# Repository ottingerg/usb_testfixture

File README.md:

# USB-C HighSpeed Test Fixture

This is a simple test fixture for testing Highspeed (USB 2.0) on USB-C Connectors

## How To Build

This board is intended to be manufactured on 2 Layers with 0.8 mm prepreg.

First prototypes are made with OSHPARK "2oz-0.8mm" process

Needed Parts:

1 pcs. Wuerth Elektronik 632712000011 (USB-C Connector)
2 pcs. Rosenberger 32K243-40ML5 (SMA Connector)

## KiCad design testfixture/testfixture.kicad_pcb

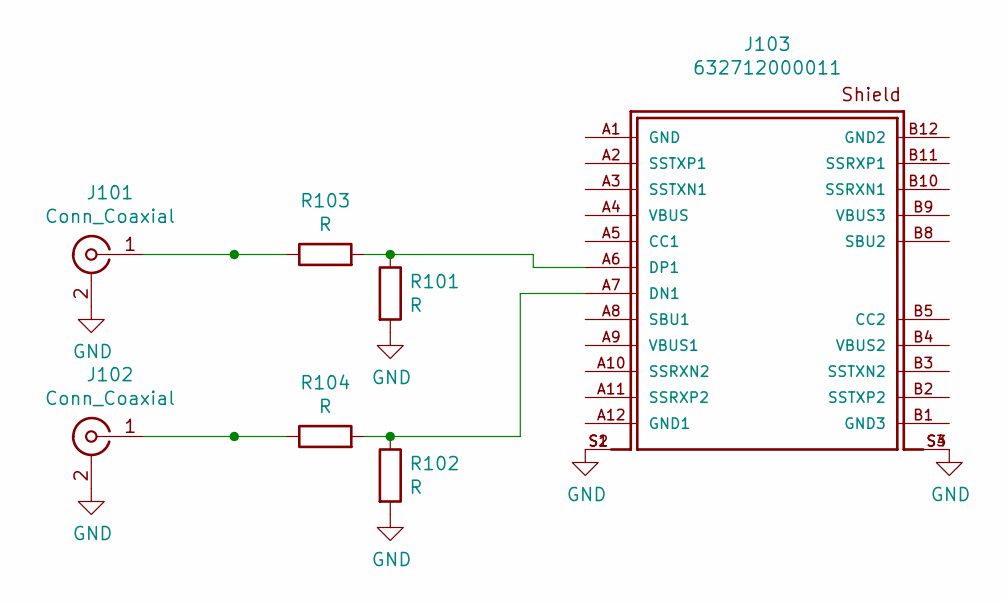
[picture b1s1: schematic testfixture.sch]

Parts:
J101, J102: Conn_Coaxial; 32K243-40ML5
J103: 632712000011; PART-NUMBER 632712000011
R101, R102, R103, R104: R; R_0402_1005Metric

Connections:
GND: J101.2 (Ext), J102.2 (Ext), J103.S1, J103.S2, J103.S3, J103.S4, R101.2, R102.2
unnamed: J101.1 (In), R103.1
unnamed: J102.1 (In), R104.1
unnamed: J103.A6 (DP1), R101.1, R103.2
unnamed: J103.A7 (DN1), R102.1, R104.2

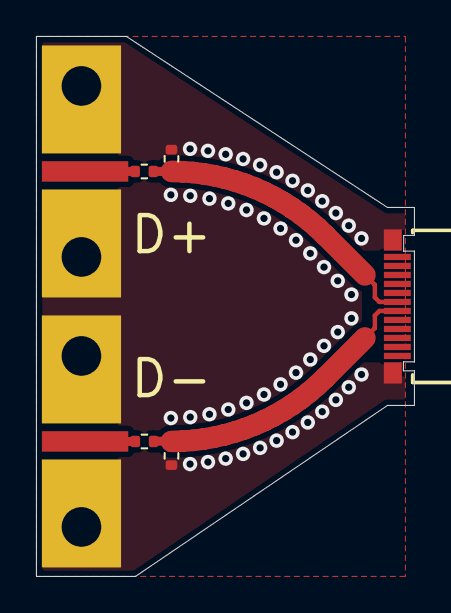
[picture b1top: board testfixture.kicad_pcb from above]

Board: 2 copper layers, 21.0 x 30.0 mm, 7 parts (0 on the bottom side), 5 nets.

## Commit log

2021-02-09 Rev.B
2022-08-08 Rev.B with Resistors and 45 Ohm matching

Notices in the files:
testfixture/testfixture.kicad_pcb:
CC BY-SA 3.0
(c) 2022
